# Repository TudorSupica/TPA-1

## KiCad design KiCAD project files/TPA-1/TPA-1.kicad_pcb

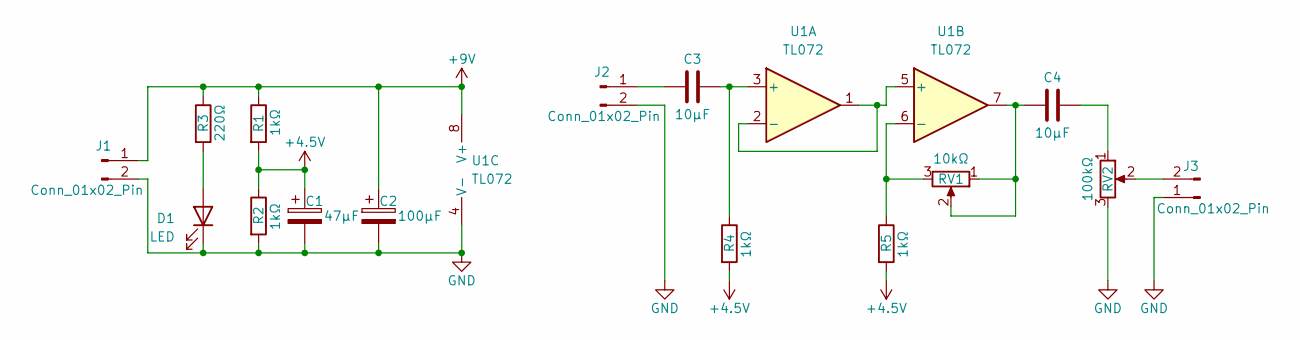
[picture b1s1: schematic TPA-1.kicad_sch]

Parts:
C1: 47µF; CP_Radial_D5.0mm_P2.00mm
C2: 100µF; CP_Radial_D5.0mm_P2.00mm
C3, C4: 10µF; C_Disc_D5.0mm_W2.5mm_P5.00mm
D1: LED; LED_D5.0mm_Clear
J1, J2, J3: Conn_01x02_Pin; PinHeader_1x02_P2.00mm_Vertical
R1, R2, R4, R5: 1kΩ; R_Axial_DIN0207_L6.3mm_D2.5mm_P7.62mm_Horizontal
R3: 220Ω; R_Axial_DIN0207_L6.3mm_D2.5mm_P7.62mm_Horizontal
RV1: 10kΩ; Potentiometer_Alpha_RD901F-40-00D_Single_Vertical
RV2: 100kΩ; Potentiometer_Alpha_RD901F-40-00D_Single_Vertical
U1: TL072; DIP-8_W7.62mm

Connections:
+4.5V: C1.1, R1.2, R2.1, R4.2, R5.2
+9V: C2.1, J1.1, R1.1, R3.1, U1.8 (V+)
GND: C1.2, C2.2, D1.1 (K), J1.2, J2.2, J3.1, R2.2, RV2.3, U1.4 (V-)
unnamed: C4.1, RV1.1, RV1.2, U1.7
unnamed: C4.2, RV2.1
unnamed: D1.2 (A), R3.2
unnamed: C3.1, J2.1
unnamed: J3.2, RV2.2
unnamed: C3.2, R4.1, U1.3 (+)
unnamed: U1.1, U1.2 (-), U1.5 (+)
unnamed: R5.1, RV1.3, U1.6 (-)

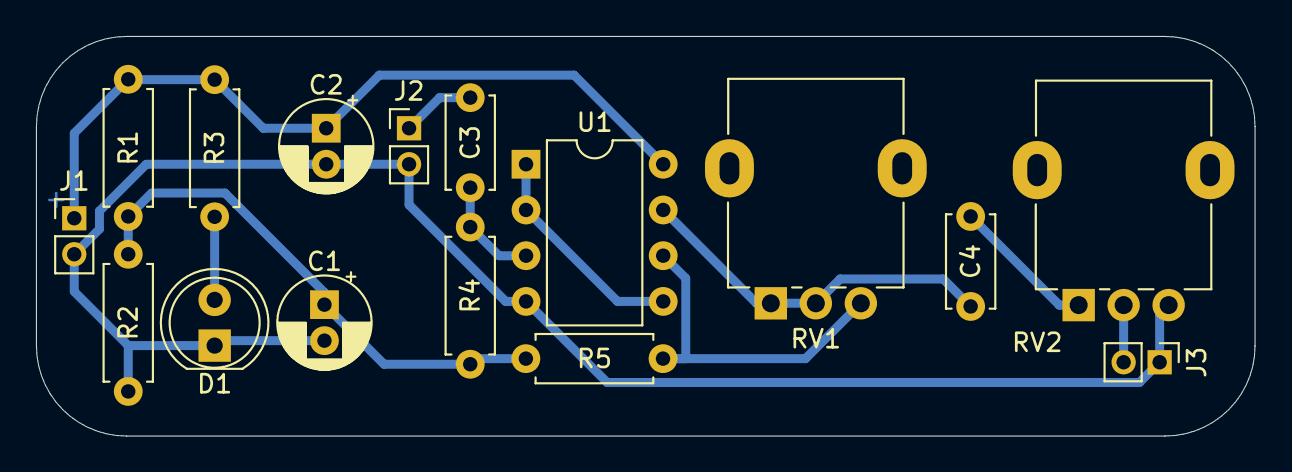
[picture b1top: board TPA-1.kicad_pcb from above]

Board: 2 copper layers, 67.7 x 22.2 mm, 16 parts (0 on the bottom side), 11 nets.

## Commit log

2024-07-24 Added schematic and PCB design
